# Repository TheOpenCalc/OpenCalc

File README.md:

This repo contains everything about OpenCalc, you can see and understand how everything is built. It should be explained in the differents README (depending on when you read this). To get more info about how you can contribute and join us you can check our website ( <a href ="opencalc.fr">opencalc.fr</a> )

## Web Simulator

Try the calculator in your browser! The firmware can be compiled to WebAssembly:

```bash
# Install Emscripten first (see WASM_BUILD.md)
source ~/emsdk/emsdk_env.sh
./firmware/wasm/build_wasm.sh

# Run the web simulator
cd web-sim
npm install
npm run dev
```

For detailed build instructions, see:
- [`WASM_BUILD.md`](WASM_BUILD.md) - How to compile the firmware to WASM
- [`web-sim/README.md`](web-sim/README.md) - Web simulator documentation

## Build Your Own

You are welcome to build and/or modify your OpenCalc (it's open source but you probably already know it if you read this) , you can choose to build everything from scratch or buy some pieces from us depending on your time and knowledge. The calculatore is made frome
<ol><li>A case which can be 3D printed </li>
<li>A PCB wich can be manufactured or homemade (in theory, we would love to hear from you if you did it)</li>
<li>A battery (we very highly advise NOT TO build it yourself from bare lithium)  </li>
<li>A raspberry pico 2 (or pi pico depending on performance you wish to have) which you can buy or build yourself</li>
<li>A screen you can buy from our website</li></ol>

If you custom your OpenCalc you can send us a message in order to share it with us, you could help build a better calculator without even knowing it.

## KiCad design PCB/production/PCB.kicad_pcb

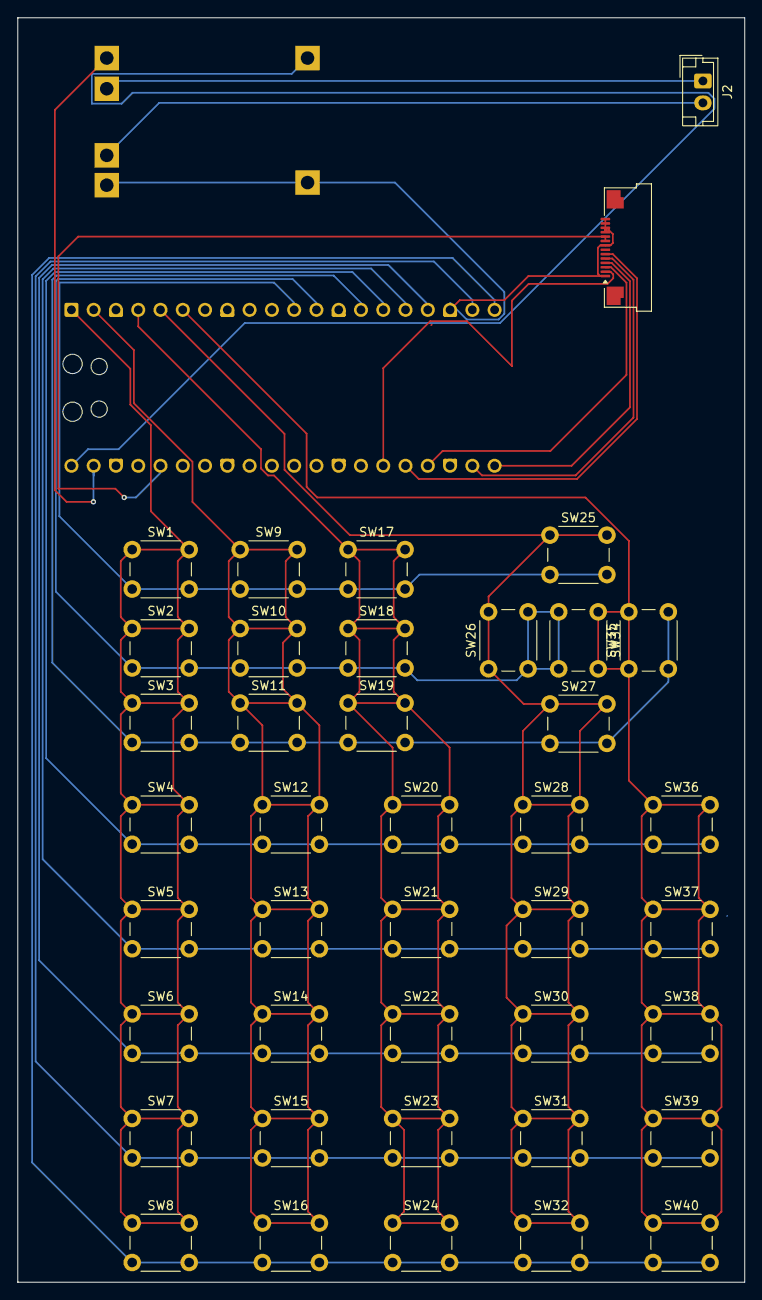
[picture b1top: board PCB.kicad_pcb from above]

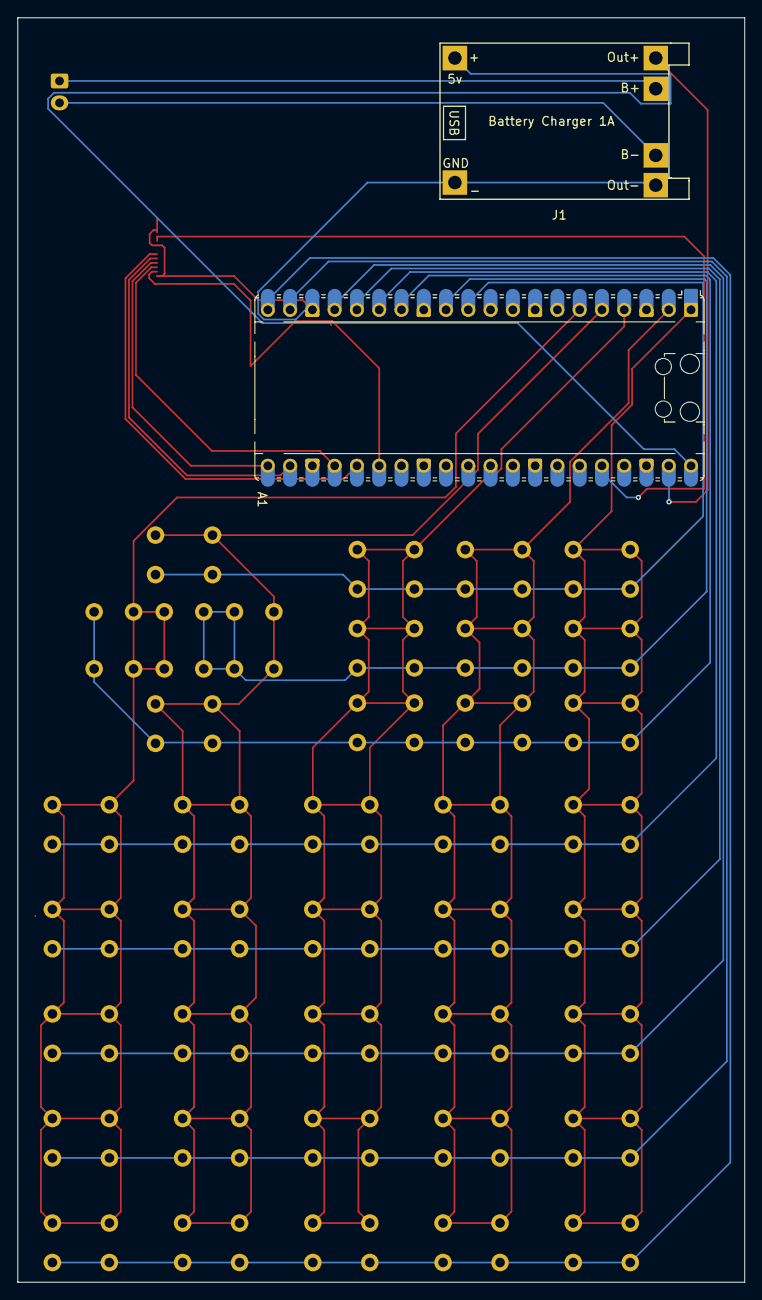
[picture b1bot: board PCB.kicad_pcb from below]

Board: 2 copper layers, 82.9 x 144.2 mm, 43 parts (2 on the bottom side), 24 nets.

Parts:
A1: RaspberryPi_Pico; RaspberryPi_Pico_Common_Unspecified
J1: TP 4056-18650; TP4056-18650
J2: Battery; JST_EH_B2B-EH-A_1x02_P2.50mm_Vertical
J4: Conn_01x14_MountingPin; Amphenol_F32Q-1A7x1-11014_1x14-1MP_P0.5mm_Horizontal
SW1: 11; SW_PUSH_6mm
SW2: 12; SW_PUSH_6mm
SW3: 13; SW_PUSH_6mm
SW4: 14; SW_PUSH_6mm
SW5: 15; SW_PUSH_6mm
SW6: 16; SW_PUSH_6mm
SW7: 17; SW_PUSH_6mm
SW8: 18; SW_PUSH_6mm
SW9: 21; SW_PUSH_6mm
SW10: 22; SW_PUSH_6mm
SW11: 23; SW_PUSH_6mm
SW12: 24; SW_PUSH_6mm
SW13: 25; SW_PUSH_6mm
SW14: 26; SW_PUSH_6mm
SW15: 27; SW_PUSH_6mm
SW16: 28; SW_PUSH_6mm
SW17: 31; SW_PUSH_6mm
SW18: 32; SW_PUSH_6mm
SW19: 33; SW_PUSH_6mm
SW20: 34; SW_PUSH_6mm
SW21: 35; SW_PUSH_6mm
SW22: 36; SW_PUSH_6mm
SW23: 37; SW_PUSH_6mm
SW24: 38; SW_PUSH_6mm
SW25: 41; SW_PUSH_6mm
SW26: 42; SW_PUSH_6mm
SW27: 43; SW_PUSH_6mm
SW28: 44; SW_PUSH_6mm
SW29: 45; SW_PUSH_6mm
SW30: 46; SW_PUSH_6mm
SW31: 47; SW_PUSH_6mm
SW32: 48; SW_PUSH_6mm
SW34: 52; SW_PUSH_6mm
SW35, SW39: 53; SW_PUSH_6mm
SW36: 54; SW_PUSH_6mm
SW37: 55; SW_PUSH_6mm
SW38: 56; SW_PUSH_6mm
SW40: 58; SW_PUSH_6mm

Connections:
+3V3: A1.36 (3V3), J4.9, J4.10
/B+: J1.5, J2.1
/B-: J1.6, J2.2
/C1: A1.1 (GPIO0), SW1.1 (C), SW2.1 (C), SW3.1 (C), SW4.1 (C), SW5.1 (C), SW6.1 (C), SW7.1 (C), SW8.1 (C)
/C2: A1.2 (GPIO1), SW9.1 (C), SW10.1 (C), SW11.1 (C), SW12.1 (C), SW13.1 (C), SW14.1 (C), SW15.1 (C), SW16.1 (C)
/C3: A1.4 (GPIO2), SW17.1 (C), SW18.1 (C), SW19.1 (C), SW20.1 (C), SW21.1 (C), SW22.1 (C), SW23.1 (C), SW24.1 (C)
/C4: A1.5 (GPIO3), SW25.1 (C), SW26.1 (C), SW27.1 (C), SW28.1 (C), SW29.1 (C), SW30.1 (C), SW31.1 (C), SW32.1 (C)
/C5: A1.6 (GPIO4), SW34.1 (C), SW35.1 (C), SW36.1 (C), SW37.1 (C), SW38.1 (C), SW39.1 (C), SW40.1 (C)
/GPIO16: A1.21 (GPIO16), J4.4
/GPIO17: A1.22 (GPIO17), J4.5
/GPIO18: A1.24 (GPIO18), J4.3
/GPIO19: A1.25 (GPIO19), J4.6
/GPIO20: A1.26 (GPIO20), J4.2
/L1: A1.20 (GPIO15), SW8.2 (D), SW16.2 (D), SW24.2 (D), SW32.2 (D), SW40.2 (D)
/L2: A1.19 (GPIO14), SW7.2 (D), SW15.2 (D), SW23.2 (D), SW31.2 (D), SW39.2 (D)
/L3: A1.17 (GPIO13), SW6.2 (D), SW14.2 (D), SW22.2 (D), SW30.2 (D), SW38.2 (D)
/L4: A1.16 (GPIO12), SW5.2 (D), SW13.2 (D), SW21.2 (D), SW29.2 (D), SW37.2 (D)
/L5: A1.15 (GPIO11), SW4.2 (D), SW12.2 (D), SW20.2 (D), SW28.2 (D), SW36.2 (D)
/L6: A1.14 (GPIO10), SW3.2 (D), SW11.2 (D), SW19.2 (D), SW27.2 (D), SW35.2 (D)
/L7: A1.12 (GPIO9), SW2.2 (D), SW10.2 (D), SW18.2 (D), SW26.2 (D), SW34.2 (D)
/L8: A1.11 (GPIO8), SW1.2 (D), SW9.2 (D), SW17.2 (D), SW25.2 (D)
/Vbus: A1.40 (VBUS), J1.1
/Vsys: A1.39 (VSYS), J1.3
GND: A1.3 (GND), A1.8 (GND), A1.13 (GND), A1.18 (GND), A1.23 (GND), A1.28 (GND), A1.38 (GND), J1.2, J1.4, J4.1, J4.8, J4.11, J4.12, J4.13, J4.14

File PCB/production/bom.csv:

Designator,Footprint,Quantity,Value,LCSC Part #
A1,RaspberryPi_Pico_Common_Unspecified,1,RaspberryPi_Pico,
SW1,SW_PUSH_6mm,1,11,
SW10,SW_PUSH_6mm,1,22,
SW11,SW_PUSH_6mm,1,23,
SW12,SW_PUSH_6mm,1,24,
SW13,SW_PUSH_6mm,1,25,
SW14,SW_PUSH_6mm,1,26,
SW15,SW_PUSH_6mm,1,27,
SW16,SW_PUSH_6mm,1,28,
SW17,SW_PUSH_6mm,1,31,
SW18,SW_PUSH_6mm,1,32,
SW19,SW_PUSH_6mm,1,33,
SW2,SW_PUSH_6mm,1,12,
SW20,SW_PUSH_6mm,1,34,
SW21,SW_PUSH_6mm,1,35,
SW22,SW_PUSH_6mm,1,36,
SW23,SW_PUSH_6mm,1,37,
SW24,SW_PUSH_6mm,1,38,
SW25,SW_PUSH_6mm,1,41,
SW26,SW_PUSH_6mm,1,42,
SW27,SW_PUSH_6mm,1,43,
SW28,SW_PUSH_6mm,1,44,
SW29,SW_PUSH_6mm,1,45,
SW3,SW_PUSH_6mm,1,13,
SW30,SW_PUSH_6mm,1,46,
SW31,SW_PUSH_6mm,1,47,
SW32,SW_PUSH_6mm,1,48,
SW34,SW_PUSH_6mm,1,52,
"SW35, SW39",SW_PUSH_6mm,2,53,
SW36,SW_PUSH_6mm,1,54,
SW37,SW_PUSH_6mm,1,55,
SW38,SW_PUSH_6mm,1,56,
SW4,SW_PUSH_6mm,1,14,
SW40,SW_PUSH_6mm,1,58,
SW5,SW_PUSH_6mm,1,15,
SW6,SW_PUSH_6mm,1,16,
SW7,SW_PUSH_6mm,1,17,
SW8,SW_PUSH_6mm,1,18,
SW9,SW_PUSH_6mm,1,21,
U5,TFT-320x240,1,TFT_320x240,

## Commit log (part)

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2025-09-23 Initial upload firmware
2025-09-23 Initial commit website without img
2025-09-23 Initial upload PCB
2025-12-05 Small update
2025-12-13 Started working more seriously on equation solver
2025-12-13 Forgot the .h
2026-01-02 Equation solver should work as intended
    Still need to adjust variables NB_VAR and NB_EQ in the switch case RIGHT Solver.cpp
2026-01-24 Delete PCB/production/backups directory
    No need to have backup on github
2026-01-24 Added KiCad files
2026-01-30 Add web-based calculator simulator
    - React + Vite web simulator for OpenCalc
    - Renders calculator firmware via WASM
    - Interactive buttons matching physical calculator layout
    - Splash screen with logo on startup
    - Keyboard support for common operations
2026-01-31 Revert "Fix WASM compilation and add framebuffer support for web simulator"
    This reverts commit 3f92bcf4a3fb2e0e76c0080557b0fe1fc6737e20.
2026-02-05 [UPD]:Code standardization, the code now conforms to the Kernighan & Ritchie standard style.
2026-02-06 New features
    Added hyperbolic trig and factorial, removed some unused code
2026-02-07 Added features
    Icons for Calc and Solver
    Hyperbolic trigonometry
    Factorial
    Buffer draw on screen (not implemented in the web sim)
2026-02-07 Bug fix
    Fixed the periodic table UI
2026-02-07 Future update
    Added a few data for the periodic table to later display
2026-02-08 wrong type solved
2026-02-08 Bug fix
    Fixed prefix display and zoom/dezoom in grapher
2026-02-09 Buf fix/ Update
    Updated the text insertion/deletion, fixed img display on web-sim
2026-02-09 Fixed some keys and tool menu
2026-02-09 Fixed img display and keys
2026-02-09 Same as previous
2026-02-09 Fix insertions
2026-02-09 Modified Ui a bit for better fit in website
2026-02-09 Added emulator link
2026-02-09 Fix img display for web sim
2026-02-09 Github have been down and has been doing weird things
2026-02-10 Add cursor blinking when graph is not shown
2026-02-11 Added icons
2026-02-11 Added (back) for periodic table
2026-02-11 Added back key
2026-02-15 Made Menu responsive + started fraction ui
2026-02-22 Updated elements
2026-02-22 Updated UI for fraction
2026-02-25 Updated emulator UI
2026-02-26 Technicaly working nested fraction display without AST
2026-03-02 free added for memory
2026-03-02 bug fixe
2026-03-02 temporary fix, 1 level of fraction in the exponent is fine
2026-03-02 Added parentehsis support
2026-03-02 Fixed decimal points display
2026-03-02 Kinda fixed Wu line
2026-03-02 added derivative to grapher
2026-03-02 Splitted ui.cpp ->0.9.1
2026-03-02 added version in html
2026-03-02 Added AST to display
2026-03-02 Bug fix
2026-03-02 Small fix
2026-03-02 test signature
2026-03-04 Solver fixed, there was some weird behavior
2026-03-07 Non linear solver + 2nd key display
2026-03-07 fixed animation main keys
2026-03-09 Added a way to display more info periodic
2026-03-09 same
2026-03-09 Added icon sequencer
2026-03-09 0.9.1->0.9.2
2026-03-09 fixed some bugs sequencer
2026-03-12 fixed bug
2026-03-13 website update
2026-03-18 Sequence Major Update 0.9.2->0.9.3
2026-03-18 0.9.2->0.9.3
2026-03-20 changed back nb display format, was no good for decimal or huge number
2026-03-20 Settings update, need to add a lot of things, UI 0.9.3->0.9.4
2026-03-22 Allowed display without overlap calc
2026-03-22 0.9.4->0.9.5
2026-03-23 automatic size fill_box in app
2026-04-04 fixed cursor diplay through nb
2026-04-28 Color in the same file
2026-04-28 fixed colors include
2026-04-28 Added infinity display
2026-04-28 automatically change position of curve grapher
2026-04-29 fixed auto center and axis moves too
2026-04-29 added credit
2026-04-29 huge bug fixed
2026-04-29 Removed debug printf
2026-04-29 changed color gradient
2026-05-06 number format
2026-05-06 don't remember why it was there but obv was not supposed
2026-05-06 recenterddec
2026-05-08 Size increase
2026-05-10 removed h from token : never used
2026-05-10 updated cursor movements
2026-05-23 now allow functions to be displayed parentheseless
2026-05-23 Limit to 27 function
2026-05-23 fixed max number function
2026-05-23 Quick add dark theme
2026-05-23 0.9.5->0.9.6
2026-05-23 Parenthesis was not doing well
2026-05-24 github link
2026-05-25 Fixed link
2026-06-11 Converter
2026-06-11 Format files
2026-06-13 revert screen clear
2026-06-20 Logo converter
2026-06-21 Img color update
2026-06-23 update color
2026-06-23 right align for results added
2026-06-25 removed placeholder
2026-06-27 sqrt display update
2026-06-30 remove /headers
